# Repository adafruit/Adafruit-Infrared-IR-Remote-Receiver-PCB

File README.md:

## Adafruit Infrared IR Remote Receiver - STEMMA JST PH 2mm PCB

<a href="http://www.adafruit.com/products/5939"><br/>
Click here to purchase one from the Adafruit shop</a>

PCB files for the Adafruit Infrared IR Remote Receiver - STEMMA JST PH 2mm. 

Format is EagleCAD schematic and board layout
* https://www.adafruit.com/product/5939

### Description

A year ago we designed a high-current-output Infrared Transmitter STEMMA which makes it easy to create high-powered IR LED blasters. Now we've sat down to design the other side, the super sensitive wide-range Adafruit Infrared IR Remote Receiver with two selectable IR receiver chips.

We found plenty of 38KHz receiver sensors that would work nicely on this breakout board - but when it came to choosing one that was vertical or horizontal we just couldn't make up our mind...so why not both? We've placed one on the end and one in the middle, and a slide switch to select which one you want to read signal from. We can't just tie the outputs together because they'd 'fight' each other and give incoherent output - but if you're willing to solder two wires, it's possible to read each one independently thanks to labelled breakout pads.

Usage is simple: Power the board by connecting V+ and ground to 3~5VDC, point a 38KHz remote control at the sensors and press some buttons. The demodulated IR envelope is piped out the Signal pin into your microcontroller which will then need to decode it. To make usage really easy, we have a green 'power good' LED and a red 'signal' LED. When IR remote signals are read by the onboard sensors, the red LED will blink to let you know.

This board will work nicely for a variety of IR remote receiving projects, and with mounting holes and a cable, a lot easier to mount in enclosures and on devices. Using a 2mm pitch STEMMA JST PH cable with headers or alligator clips on the end, you can easily wire this board without any soldering.

Note that this board is specifically for receiving 38KHz IR remote control signals - it isn't going to work for proximity/distance sensing or other frequency signals. The signal must be read by a microcontroller that has pulse-input reading capabilities - basically just check that it supports common IR Receiver connectivity and decoding. Sometimes you need to use special code or pins.

Each STEMMA board is a fully assembled and tested PCB but no cable. No soldering is required to use it, but you will need to pick up a 2mm pitch, 3-pin STEMMA JST PH cable. Alternatively, if you do want to solder, there's a 0.1" spaced header for power/ground/signal.

### License

Adafruit invests time and resources providing this open source design, please support Adafruit and open-source hardware by purchasing products from [Adafruit](https://www.adafruit.com)!

Designed by Limor Fried/Ladyada for Adafruit Industries.

Creative Commons Attribution/Share-Alike, all text above must be included in any redistribution. 
See license.txt for additional details.

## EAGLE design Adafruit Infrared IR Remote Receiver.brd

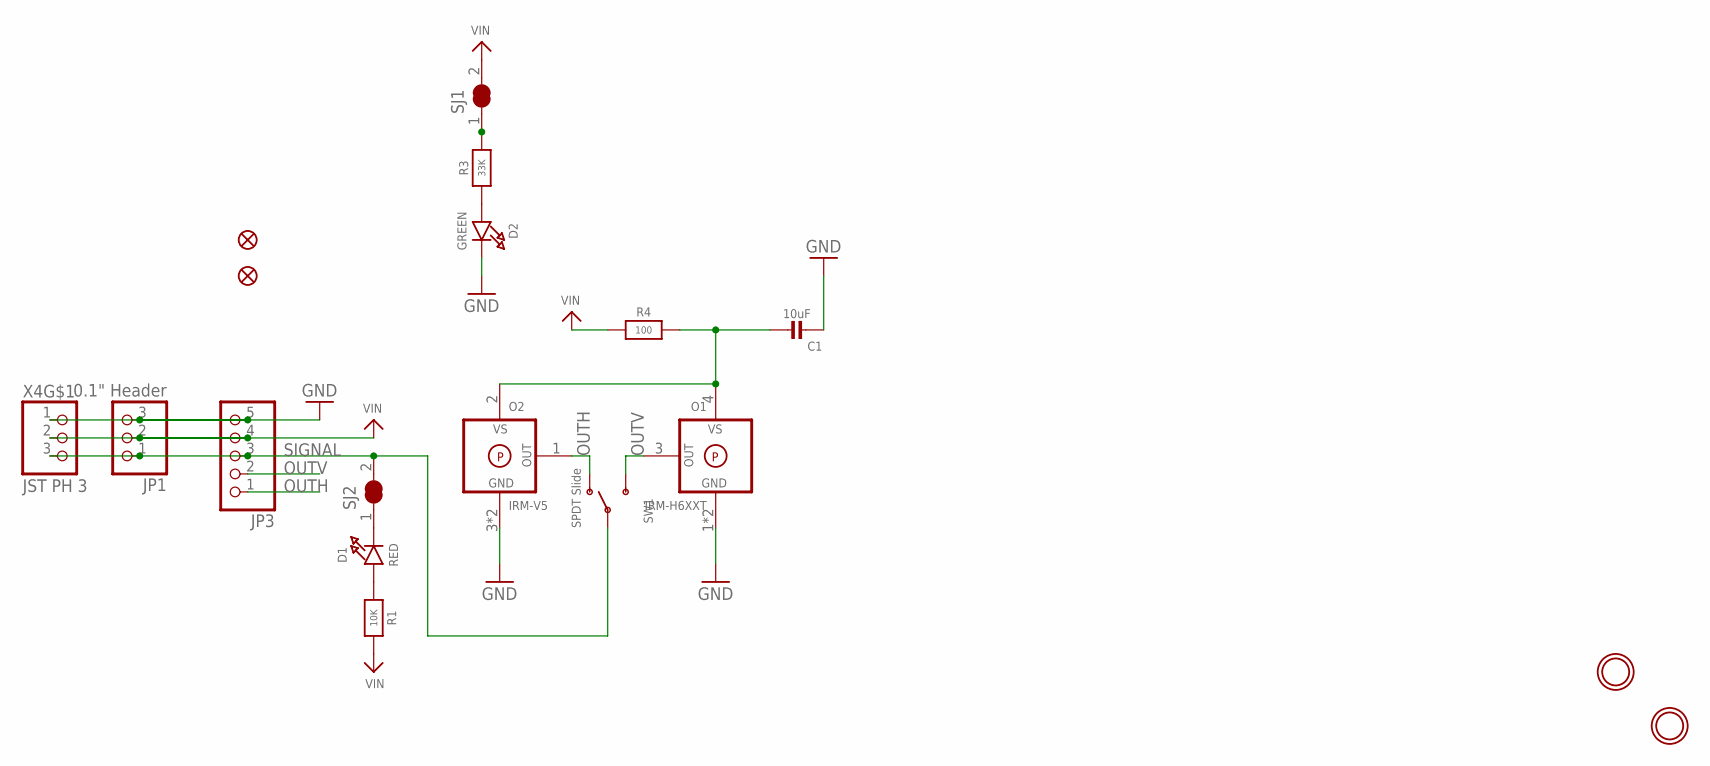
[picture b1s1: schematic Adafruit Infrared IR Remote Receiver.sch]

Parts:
C1: 10uF; 0805-NO
D1: RED; CHIPLED_0603_NOOUTLINE
D2: GREEN; CHIPLED_0603_NOOUTLINE
FID2, FID3: FIDUCIAL_1MM
JP1: 0.1" Header; 1X03_OVAL
JP3: HEADER-1X570MIL; 1X05_ROUND_70
O1: IRM-H6XXT
O2: IRM-V5
R1: 10K; 0603-NO
R3: 33K; 0603-NO
R4: 100; 0603-NO
SJ1, SJ2: SOLDERJUMPER_CLOSED; SOLDERJUMPER_CLOSEDWIRE
SW1: SPDT Slide; SPDT_SMT_SSSS811101
U$1, U$8: MOUNTINGHOLE2.5; MOUNTINGHOLE_2.5_PLATED
X4: JST PH 3; JSTPH3

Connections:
GND: C1.2, D2.C, JP1.3, JP3.5, O1.1 (GND), O1.2 (GND), O2.3 (GND), O2.MT (GND), X4.1
unnamed: R3.2, SJ1.1
unnamed: D1.A, R1.1
unnamed: D1.C, SJ2.1
unnamed: C1.1, O1.4 (VS), O2.2 (VS), R4.2
unnamed: D2.A, R3.1
OUTH: JP3.1, O2.1 (OUT), SW1.A (O)
OUTV: JP3.2, O1.3 (OUT), SW1.C (S)
SIGNAL: JP1.1, JP3.3, SJ2.2, SW1.B, X4.3
VIN: JP1.2, JP3.4, R1.2, R4.1, SJ1.2, X4.2

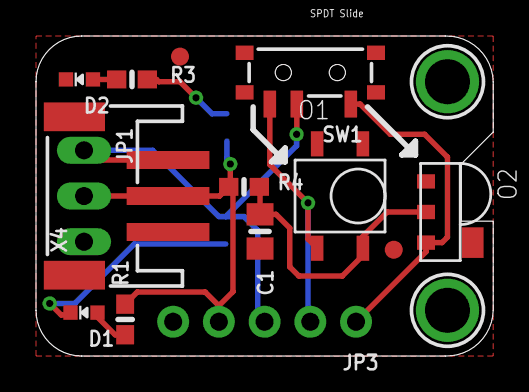
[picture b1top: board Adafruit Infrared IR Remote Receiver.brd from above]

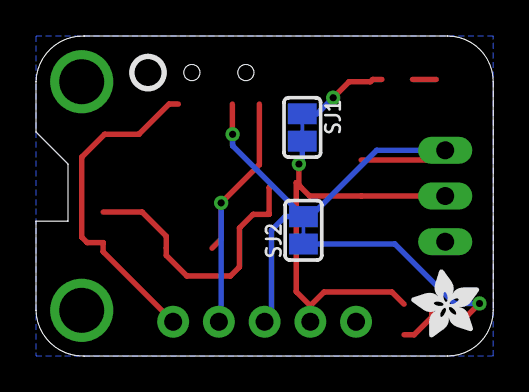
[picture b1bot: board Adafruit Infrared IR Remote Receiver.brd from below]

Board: 2 copper layers, 25.4 x 17.8 mm, 37 parts (16 on the bottom side), 10 nets.

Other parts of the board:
PLABEL0: PLABEL0
PLABEL1: PLABEL1
PLABEL2, PLABEL14: PLABEL14
PLABEL3, PLABEL13: PLABEL13
PLABEL5: PLABEL5
PLABEL15: PLABEL15
PLABEL16: PLABEL16
PLABEL17: PLABEL17
PLABEL18: PLABEL18
PLABEL19: PLABEL19
PLABEL20: PLABEL20
PLABEL21: PLABEL21
PLABEL22: PLABEL22
PLABEL23: PLABEL23
PLABEL24: PLABEL24
U$5: PCBFEAT-REV-040
U$10: ADAFRUIT_3.5MM

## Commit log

2024-04-16 cookiecutter

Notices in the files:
parts and their libraries:
microbuilder: This work is placed in the public domain, and may be freely used for commercial and non-commercial work with the following conditions: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
